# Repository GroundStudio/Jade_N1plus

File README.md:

GroundStudio Jade N1+
====================================

Get it from [ardushop.ro](https://ardushop.ro/en/groundstudio/1403-jade-n1-rev100-6427854020598.html)

Explore all the GroundStudio products at [ardushop.ro](https://ardushop.ro/en/37-groundstudio)

Description
-------------------
ATMEGA328PB based development board featuring picoPower® technology for better power management, Peripheral Touch Controller (PTC), 32kBytes of In-System Self-Programmable Flash program memory,  1kBytes EEPROM, 2kBytes Internal SRAM, 9 PWM Channels, 22 Digital Pins, 2 USART, 2 SPI, 2 I²C, 8 ADC Pins with 10 bit Resolution and HT42B534-2 for USB comunication.

Contents
-------------------

* [/Documentation](https://github.com/GroundStudio/Jade_N1plus/tree/main/Documentation) -- Pinout.
* [/Hardware](https://github.com/GroundStudio/Jade_N1plus/tree/main/Hardware) -- Schematics, layout.

Versions
-------------------
*(Not all tags shown)*
- [REV1.0.0]:

License
-------------------

This is released under the [Attribution-ShareAlike 4.0 International (CC BY-SA 4.0)](https://creativecommons.org/licenses/by-sa/4.0/) license. 
**You are welcome to use this for commercial purposes.**

Please consider contributing back to this project or others to help the open-source hardware community continue to thrive and grow! 

Certifications:

[Open Source Hardware Association](https://certification.oshwa.org/ro000023.html)   
   
[
](https://certification.oshwa.org/ro000023.html)

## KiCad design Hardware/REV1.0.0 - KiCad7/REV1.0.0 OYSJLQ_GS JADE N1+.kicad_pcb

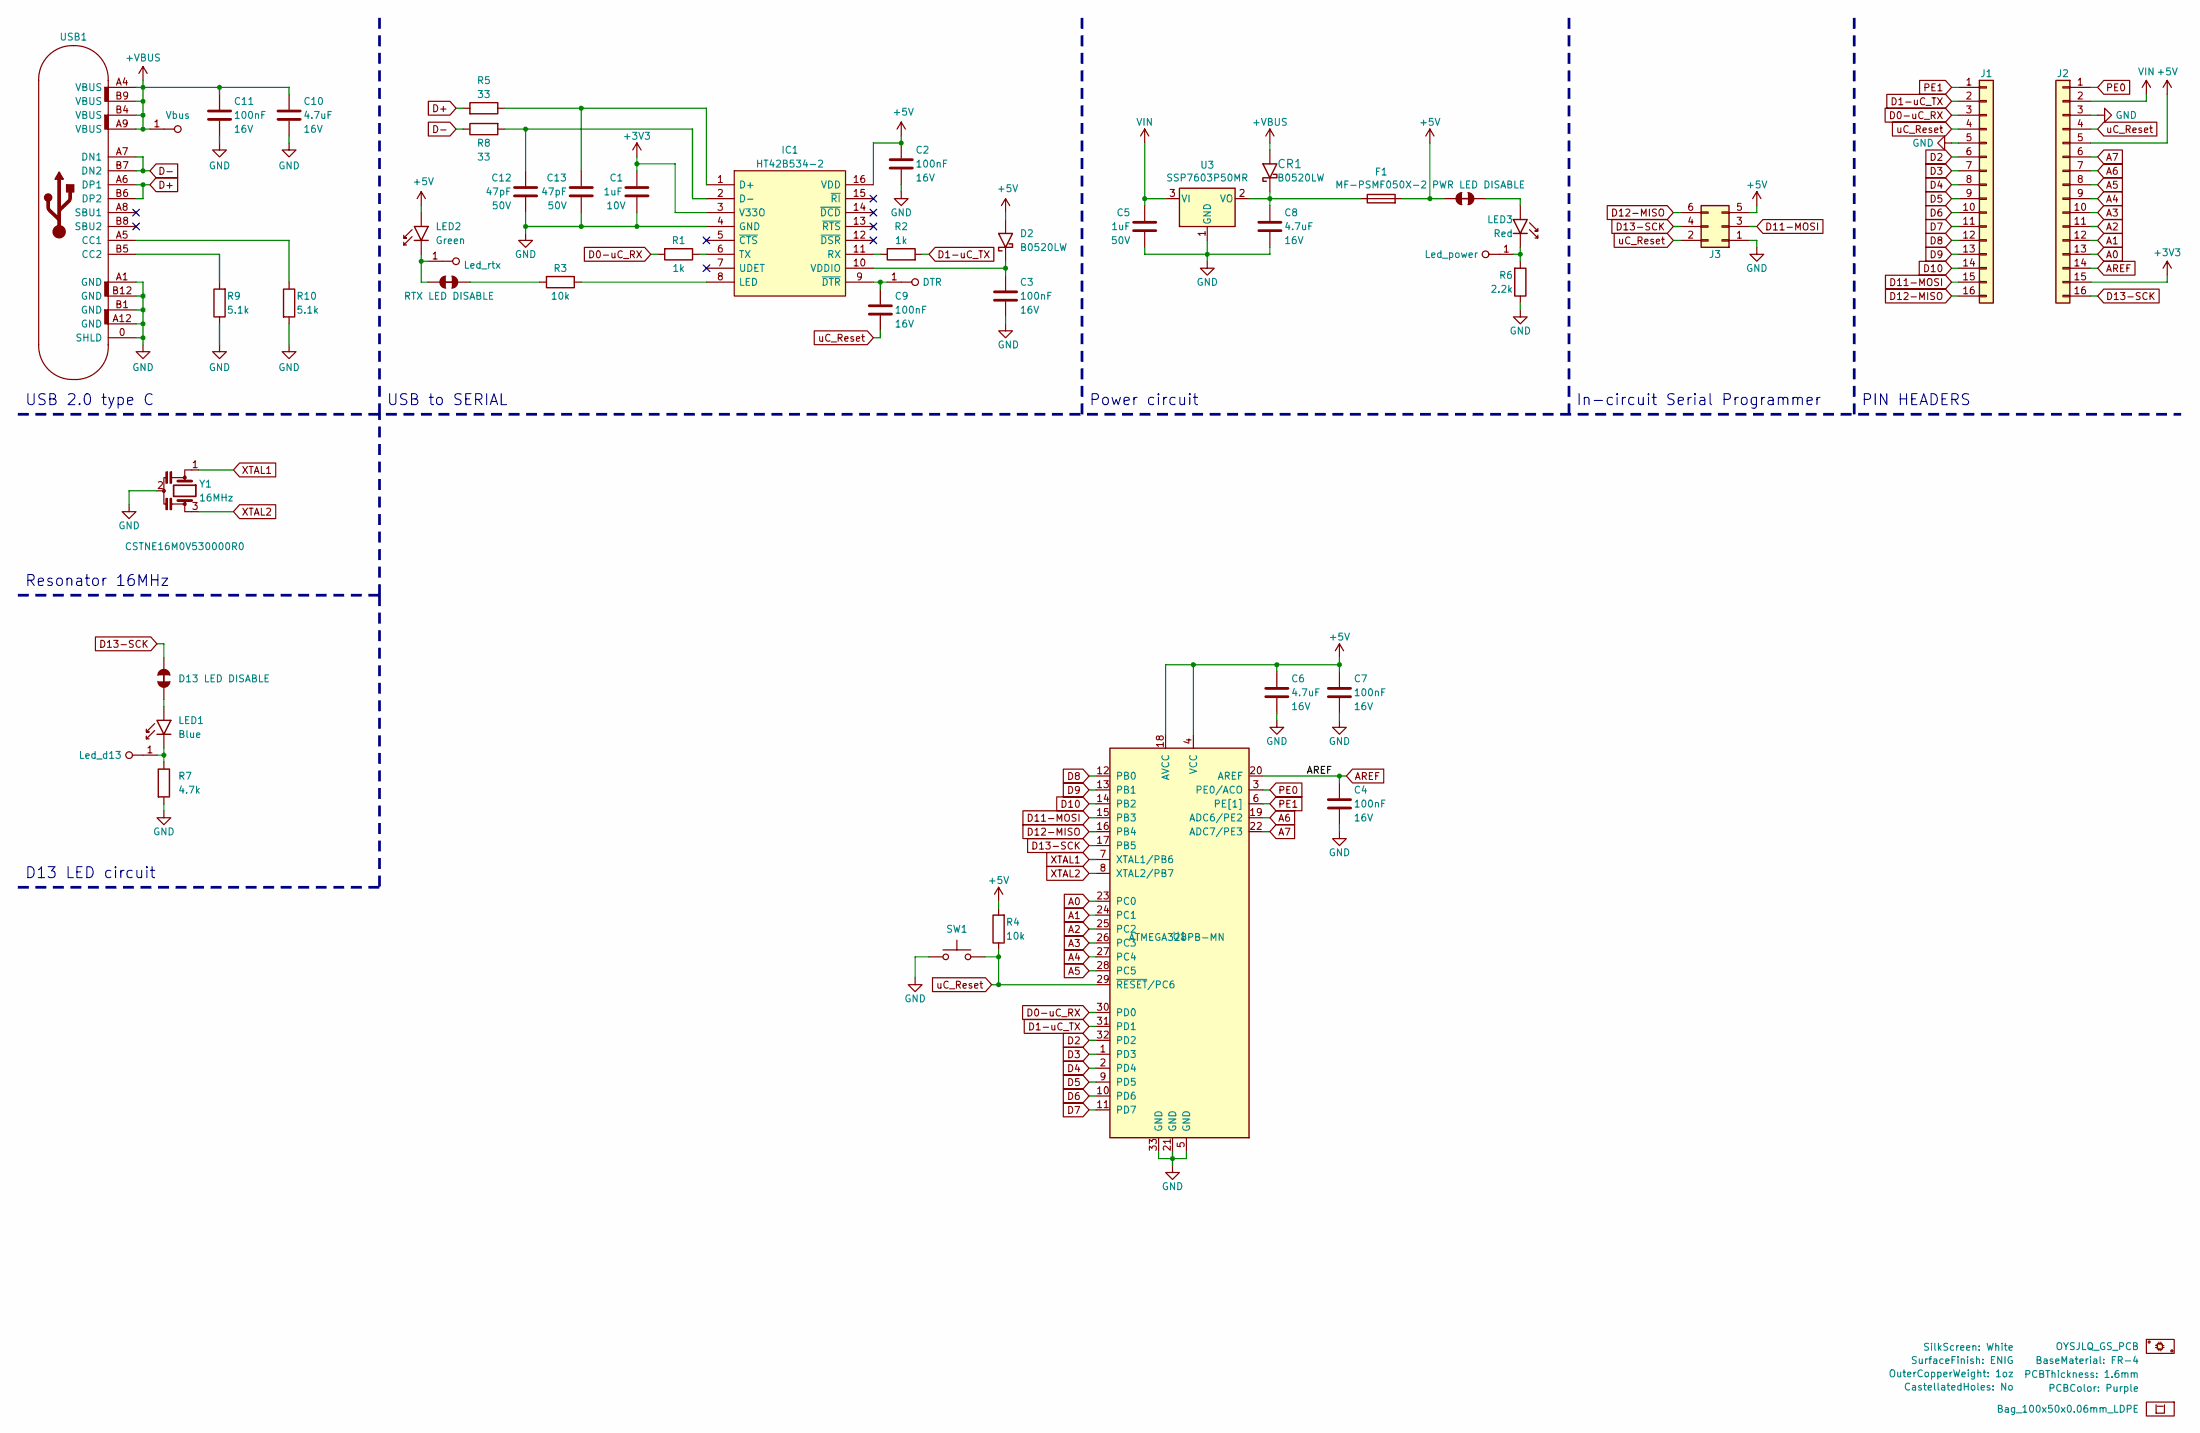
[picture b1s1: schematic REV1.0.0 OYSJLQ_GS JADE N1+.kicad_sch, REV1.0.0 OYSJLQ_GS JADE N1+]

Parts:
B1: Bag_100x50x0.06mm_LDPE; MPN KFHHEG_B
C1: C_0402_1uF_10V; C_0402_alt; Rated voltage 10V; MPN FS15B105K100PKG; LCSC C525324
C2, C4, C7, C9, C11: C_0402_100nF_16V; C_0402_alt; Rated voltage 16V; MPN 0402B104K160CT; LCSC C83056
C3: C_0402_100nF_16V; C_0402_alt; MPN 0402B104K160CT; LCSC C83056
C5: C_0603_1uF_50V; C_0603; Rated voltage 50V; MPN CL10A105KB8NNNC; LCSC C15849
C6, C8, C10: C_0402_4.7uF_16V; C_0402_alt; Rated voltage 16V; MPN C0402X5R475M160NT; LCSC C729453
C12, C13: C_0402_47pF_50V; C_0402_alt; Rated voltage 50V; MPN FN15N470J500PNG; LCSC C525215
CR1: SOD-123 B0520LW; SOD-123; MPN B0520LW; LCSC C89640
D2: SOD-123 B0520LW; SOD-123; MPN B0520LW; LCSC C89640
F1: Fuse_0805_MF-PSMF050X-2; Fuse_0805; MPN MF-PSMF050X-2; LCSC C116170
IC1: SOP-16_150MIL HT42B534-2; SOP-16_150MIL; MPN HT42B534-2; LCSC C493361
J1, J2: PinHeader_1x16_P2.54_V_M; PinHeader_1x16_P2.54mm_Vertical_Male; MPN KH-2.54PH180-1X16P-L11.5; LCSC C2905491
J3: PinHeader_2x03_P2.54_V_M; PinHeader_2x03_P2.54mm_Vertical_Male; MPN 210-72-03GB01; LCSC C402781
J4: D13 LED DISABLE; SolderJumper_NC_Default
J5: RTX LED DISABLE; SolderJumper_NC_Default
J6: PWR LED DISABLE; SolderJumper_NC_Default
LED1: LED_0402_BLUE; LED_0402_alt; MPN TZ-P2-0402BTIA1-0.45T; LCSC NA
LED2: LED_0402_GREEN; LED_0402_alt; MPN TZ-P2-0402GTIA1-0.45T; LCSC C688877
LED3: LED_0402_RED; LED_0402_alt; MPN TZ-P2-0402RTIA1-0.45T; LCSC C779449
P1: PCB; MPN OYSJLQ_GS_PCB
R1, R2: R_0402_1k; R_0402_alt; MPN RC-02W1001FT; LCSC C226166
R3, R4: R_0402_10k; R_0402_alt; MPN 0402WGJ0103TCE; LCSC C25531
R5, R8: R_0402_33; R_0402_alt; MPN RC-02W33R0FT; LCSC C140161
R6: R_0402_2.2k; R_0402_alt; MPN RC-02W2201FT; LCSC C258093
R7: R_0402_4.7k; R_0402_alt; MPN WR04X4701FTL; LCSC C163826
R9, R10: R_0402_5.1k; R_0402_alt; MPN RC-02W5101FT; LCSC C294638
SW1: TS342A2P-WZ; MPN TS342A2P-WZ; LCSC C557591
TP1: Led_rtx; TestPoint
TP2: Led_power; TestPoint
TP3: Vbus; TestPoint
TP4: Led_d13; TestPoint
TP5: DTR; TestPoint
U1: ATmega328PB-MUR; QFN-32-1EP_5x5_P0.5_EP3.1x3.1; MPN ATMEGA328PB-MN; LCSC C1337164
U3: SOT-23-3 SSP7603P50MR; SOT-23-3; MPN SSP7603P50MR; LCSC C411029
USB1: USB_C_FULL; USB_C_C167321; MPN 918-418K2023S40001; LCSC C167321
Y1: RSN_3P_3.2x1.3 CSTNE16M0V; Rsn_muRata_CSTxE-3Pin_3.2x1.3mm; MPN CSTNE16M0V530000R0; LCSC C341521

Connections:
+3V3: C1.1, IC1.3 (V33O), J2.15
+5V: C2.2, C6.1, C7.1, D2.2 (A), F1.2, IC1.16 (VDD), J2.5, J3.5, J6.2, LED2.2 (A), R4.2, U1.4 (VCC), U1.18 (AVCC)
+VBUS: C10.1, C11.1, CR1.2 (A), TP3.1, USB1.A4 (VBUS), USB1.A9 (VBUS), USB1.B4 (VBUS), USB1.B9 (VBUS)
A0: J2.13, U1.23 (PC0)
A1: J2.12, U1.24 (PC1)
A2: J2.11, U1.25 (PC2)
A3: J2.10, U1.26 (PC3)
A4: J2.9, U1.27 (PC4)
A5: J2.8, U1.28 (PC5)
A6: J2.7, U1.19 (ADC6/PE2)
A7: J2.6, U1.22 (ADC7/PE3)
AREF: C4.1, J2.14, U1.20 (AREF)
D0-uC_RX: J1.3, R1.2, U1.30 (PD0)
D1-uC_TX: J1.2, R2.2, U1.31 (PD1)
D2: J1.6, U1.32 (PD2)
D3: J1.7, U1.1 (PD3)
D4: J1.8, U1.2 (PD4)
D5: J1.9, U1.9 (PD5)
D6: J1.10, U1.10 (PD6)
D7: J1.11, U1.11 (PD7)
D8: J1.12, U1.12 (PB0)
D9: J1.13, U1.13 (PB1)
D10: J1.14, U1.14 (PB2)
D11-MOSI: J1.15, J3.3, U1.15 (PB3)
D12-MISO: J1.16, J3.6, U1.16 (PB4)
D13-SCK: J2.16, J3.4, J4.1, U1.17 (PB5)
D+: R5.2, USB1.A6 (DP1), USB1.B6 (DP2)
D-: R8.1, USB1.A7 (DN1), USB1.B7 (DN2)
GND: C1.2, C2.1, C3.1, C4.2, C5.2, C6.2, C7.2, C8.2, C10.2, C11.2, C12.1, C13.2, IC1.4 (GND), J1.5, J2.3, J3.1, R6.1, R7.2, R9.1, R10.2, SW1.1, U1.5 (GND), U1.21 (GND), U1.33 (GND), U3.1 (GND), USB1.0 (SHLD), USB1.A1 (GND), USB1.A12 (GND), USB1.B1 (GND), USB1.B12 (GND), Y1.2
unnamed: C8.1, CR1.1 (K), F1.1, U3.2 (VO)
unnamed: C3.2, D2.1 (K), IC1.10 (VDDIO)
unnamed: C13.1, IC1.1 (D+), R5.1
unnamed: C12.2, IC1.2 (D-), R8.2
unnamed: IC1.8 (LED), R3.1
unnamed: IC1.11 (RX), R2.1
unnamed: IC1.6 (TX), R1.1
unnamed: C9.2, IC1.9 (~DTR), TP5.1
unnamed: J5.2, R3.2
unnamed: J4.2, LED1.2 (A)
unnamed: LED1.1 (K), R7.1, TP4.1
unnamed: J5.1, LED2.1 (K), TP1.1
unnamed: J6.1, LED3.2 (A)
unnamed: LED3.1 (K), R6.2, TP2.1
unnamed: R10.1, USB1.A5 (CC1)
unnamed: R9.2, USB1.B5 (CC2)
PE0: J2.1, U1.3 (PE0/ACO)
PE1: J1.1, U1.6 (PE[1])
VIN: C5.1, J2.2, U3.3 (VI)
XTAL1: U1.7 (XTAL1/PB6), Y1.1
XTAL2: U1.8 (XTAL2/PB7), Y1.3
uC_Reset: C9.1, J1.4, J2.4, J3.2, R4.1, SW1.2, U1.29 (~RESET/PC6)

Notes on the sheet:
Resonator 16MHz
PIN HEADERS
USB 2.0 type C
Power circuit
D13 LED circuit
In-circuit Serial Programmer
USB to SERIAL

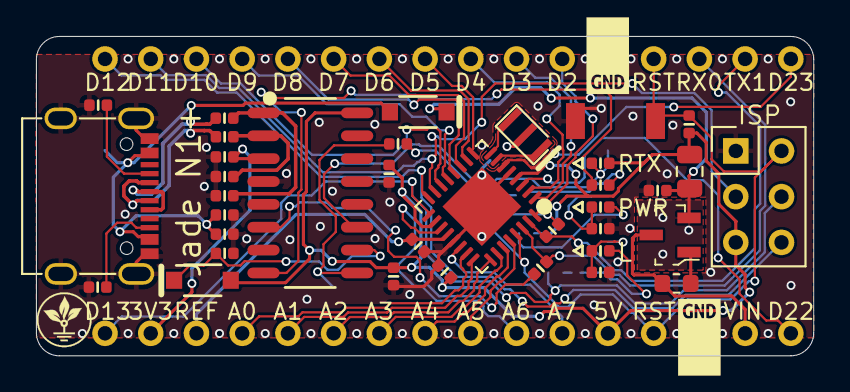
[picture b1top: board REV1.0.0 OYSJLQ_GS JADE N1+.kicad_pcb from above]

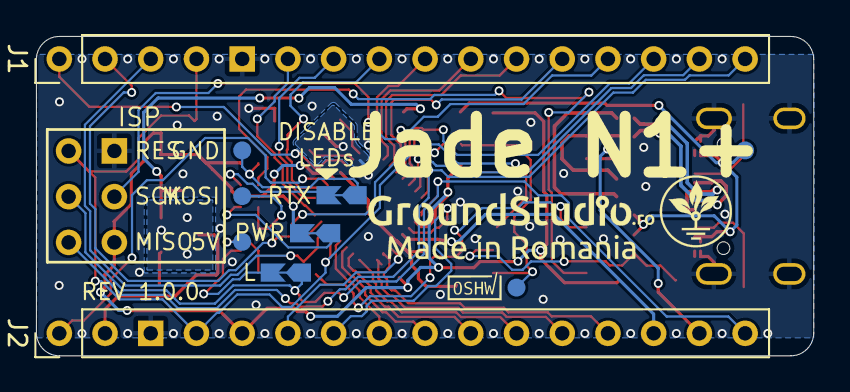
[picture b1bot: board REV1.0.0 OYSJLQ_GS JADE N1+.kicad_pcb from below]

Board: 2 copper layers, 43.2 x 17.7 mm, 48 parts (5 on the bottom side), 51 nets.

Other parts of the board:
kibuzzard-6597D01D: G***; kibuzzard-6597D01D
kibuzzard-6597D047: G***; kibuzzard-6597D047

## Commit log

2024-01-31 - added pinout, schematic and kicad files
2025-09-10 update shop links
